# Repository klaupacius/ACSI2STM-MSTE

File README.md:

# ACSI2STM-MSTE
 
This a KiCAD (6.0) design to host an [ACSI2STM](https://github.com/retro16/acsi2stm) directly inside an Atari Mega STE using the internal connector. 
The PCB has been designed to accomodate version 2.43 of ACSI2STM (aka V2) but also the V1 design as sold by @masteries on AtariAge. 
- No external power is required, the 5v is taken directly from the internal ACSI connector, but this has only been tested with a fully recapped PSU. 
- A set of jumper needs to be soldered to configure the board for V1 or V2 as noted on the PCB.

:warning: **DO NOT PLUG ANY USB CABLE ON THE STM32 ONCE INSTALLED IN THE MEGA STE** :warning:

## BOM
- 100 nF Capacitor
- 10uF Radial Capacitor
- Female 2.54 headers
- Amphenol GSD090012SEU SD Card socket
- STM32F103C8T6 "Blue Pill" (original one is highly recommended!!!). 
- Firmware from [ACSI2STM](https://github.com/retro16/acsi2stm) or from @masteries. 

## Configuration
Configuration is done by simple solder bridges on the pads, instructions are also written on PCB.

### For V1:
- Solder bridge: JP1, JP2, JP3, JP4, JP5, JP6, JP7
- Solder bridge pads 1 and 2 of JP9 (2 leftmost pads)
- Solder bridge pads 1 and 2 of JP10 (2 leftmost pads)

### For V2: 
- Solder bridge pads 2 and 3 of JP9 (2 leftmost pads)
- Solder bridge pads 2 and 3 of JP10 (2 leftmost pads)
- Solder bridge JP8 (optional but recommended)

:warning: **DO NOT PLUG ANY USB CABLE ON THE STM32 ONCE INSTALLED IN THE MEGA STE** :warning:

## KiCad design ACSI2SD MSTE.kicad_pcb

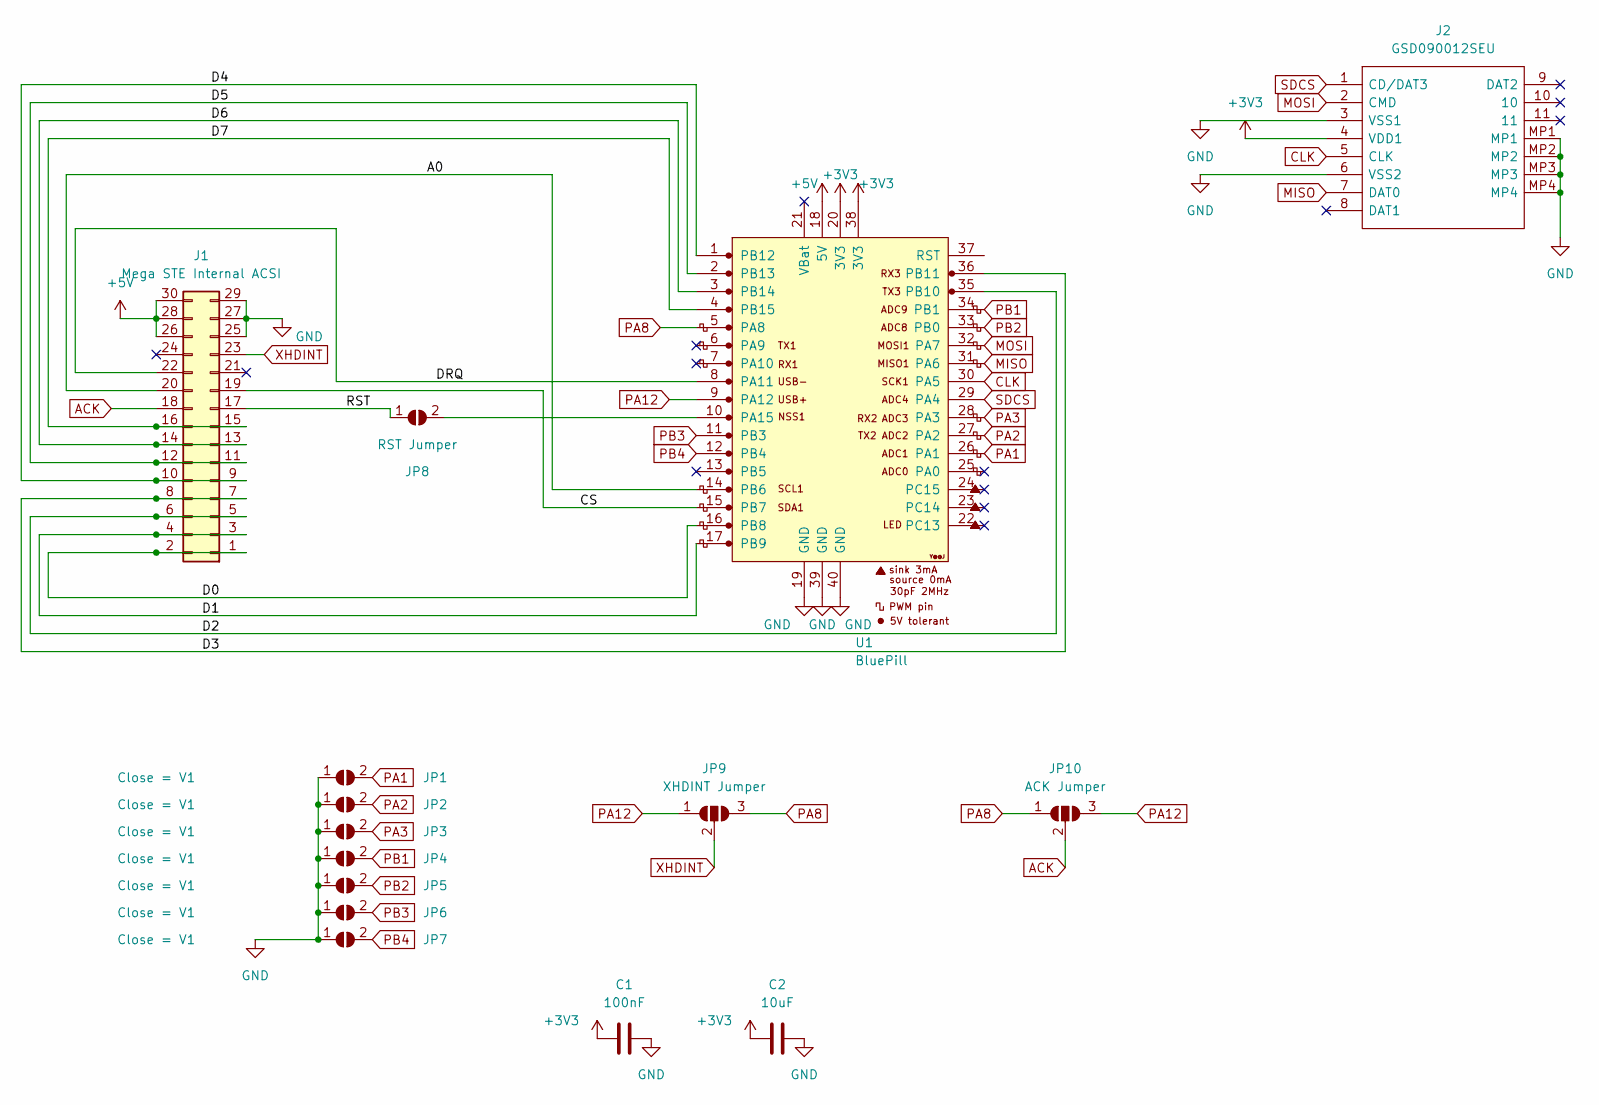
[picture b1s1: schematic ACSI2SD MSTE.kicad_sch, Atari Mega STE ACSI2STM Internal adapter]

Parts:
C1: 100nF; C_Disc_D4.3mm_W1.9mm_P5.00mm
C2: 10uF; C_Radial_D5.0mm_H5.0mm_P2.00mm
J1: Mega STE Internal ACSI; PinSocket_2x15_P2.54mm_Vertical
J2: GSD090012SEU; Mouser Part Number 523-GSD090012SEU
JP1, JP2, JP3, JP4, JP5, JP6, JP7: Close = V1; SolderJumper-2_P1.3mm_Open_Pad1.0x1.5mm
JP8: RST Jumper; SolderJumper-2_P1.3mm_Open_RoundedPad1.0x1.5mm
JP9: XHDINT Jumper; SolderJumper-3_P1.3mm_Open_RoundedPad1.0x1.5mm
JP10: ACK Jumper; SolderJumper-3_P1.3mm_Open_RoundedPad1.0x1.5mm
U1: BluePill; YAAJ_BluePill_1

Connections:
+3V3: C1.1, C2.1, J2.4 (VDD1), U1.20 (3V3), U1.38 (3V3)
+5V: J1.26, J1.28, J1.30, U1.18 (5V)
/A0: J1.20, U1.14 (PB6)
/CS: J1.19, U1.15 (PB7)
/D0: J1.1, J1.2, U1.16 (PB8)
/D1: J1.3, J1.4, U1.17 (PB9)
/D2: J1.5, J1.6, U1.35 (PB10)
/D3: J1.7, J1.8, U1.36 (PB11)
/D4: J1.9, J1.10, U1.1 (PB12)
/D5: J1.11, J1.12, U1.2 (PB13)
/D6: J1.13, J1.14, U1.3 (PB14)
/D7: J1.15, J1.16, U1.4 (PB15)
/DRQ: J1.22, U1.8 (PA11)
/RST: J1.17, JP8.1 (A)
ACK: J1.18, JP10.2 (C)
CLK: J2.5 (CLK), U1.30 (PA5)
GND: C1.2, C2.2, J1.25, J1.27, J1.29, J2.3 (VSS1), J2.6 (VSS2), J2.MP1, J2.MP2, J2.MP3, J2.MP4, JP1.1 (A), JP2.1 (A), JP3.1 (A), JP4.1 (A), JP5.1 (A), JP6.1 (A), JP7.1 (A), U1.19 (GND), U1.39 (GND), U1.40 (GND)
MISO: J2.7 (DAT0), U1.31 (PA6)
MOSI: J2.2 (CMD), U1.32 (PA7)
unnamed: JP8.2 (B), U1.10 (PA15)
PA1: JP1.2 (B), U1.26 (PA1)
PA2: JP2.2 (B), U1.27 (PA2)
PA3: JP3.2 (B), U1.28 (PA3)
PA8: JP9.3 (B), JP10.1 (A), U1.5 (PA8)
PA12: JP9.1 (A), JP10.3 (B), U1.9 (PA12)
PB1: JP4.2 (B), U1.34 (PB1)
PB2: JP5.2 (B), U1.33 (PB0)
PB3: JP6.2 (B), U1.11 (PB3)
PB4: JP7.2 (B), U1.12 (PB4)
SDCS: J2.1 (CD/DAT3), U1.29 (PA4)
XHDINT: J1.23, JP9.2 (C)

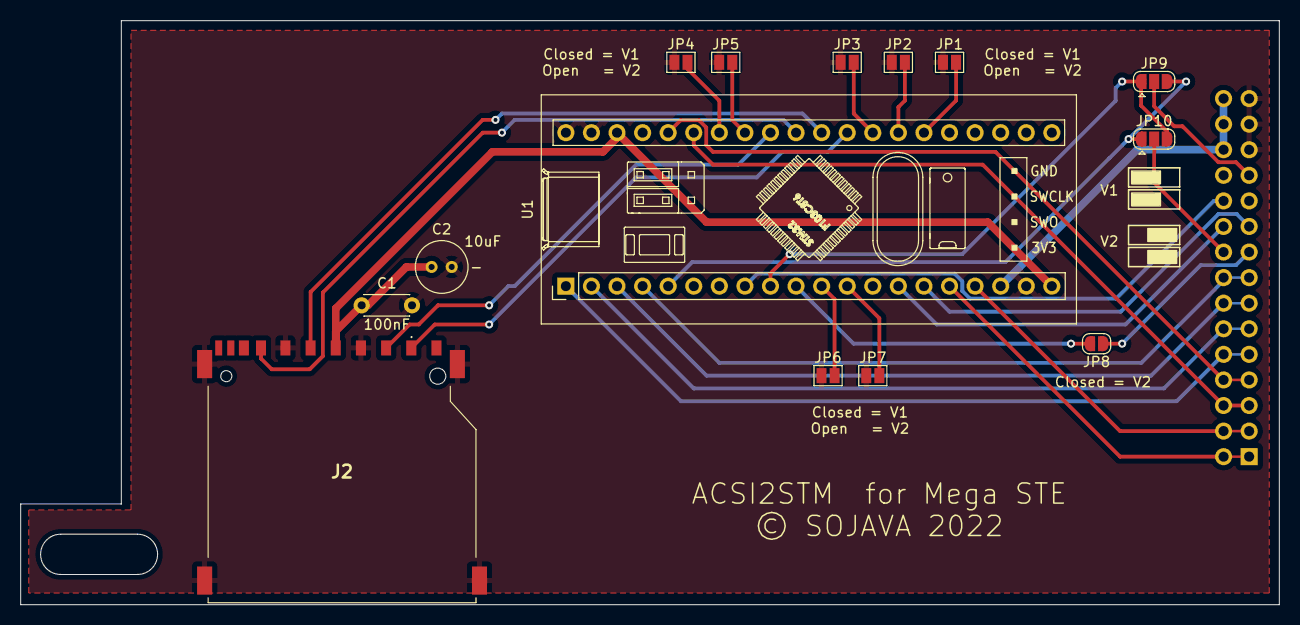
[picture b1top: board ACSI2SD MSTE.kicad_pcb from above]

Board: 2 copper layers, 125.0 x 58.0 mm, 15 parts (1 on the bottom side), 31 nets.

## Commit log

2022-04-15 cleaned repository

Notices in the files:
ACSI2SD MSTE.kicad_pcb:
© SOJAVA 2022
